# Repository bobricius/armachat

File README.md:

# ARMACHAT
# My network = my rules, no borders, no limits, no operators.

Full time step by step - soldering, programming, assembly

Standalone Doomsday LORA QWERTY communicator

How to restore communication after disaster or Armageddon ? 

It is just hi-tech walkie talkie for fun :)

# Hardware features:

- SAMD21G18 for desktop version (pocket version use SAMD21E18, more easy to solder in TQFP32)
- QWERTY keyboard
 40 keys (4x10) desktop version
 30 keys (5x6) pocket version
- 18650 li-on battery
- 1.8 TFT LCD display 128x160 ST7735
- RFM95 lora module
- 3 freq. by your country
- IRQ / wake up
- Beeper
- Battery charging
- Software RTC with alarms

I shortly tested this messenger in my village and distance is about 500m without direct sight with spread 9.

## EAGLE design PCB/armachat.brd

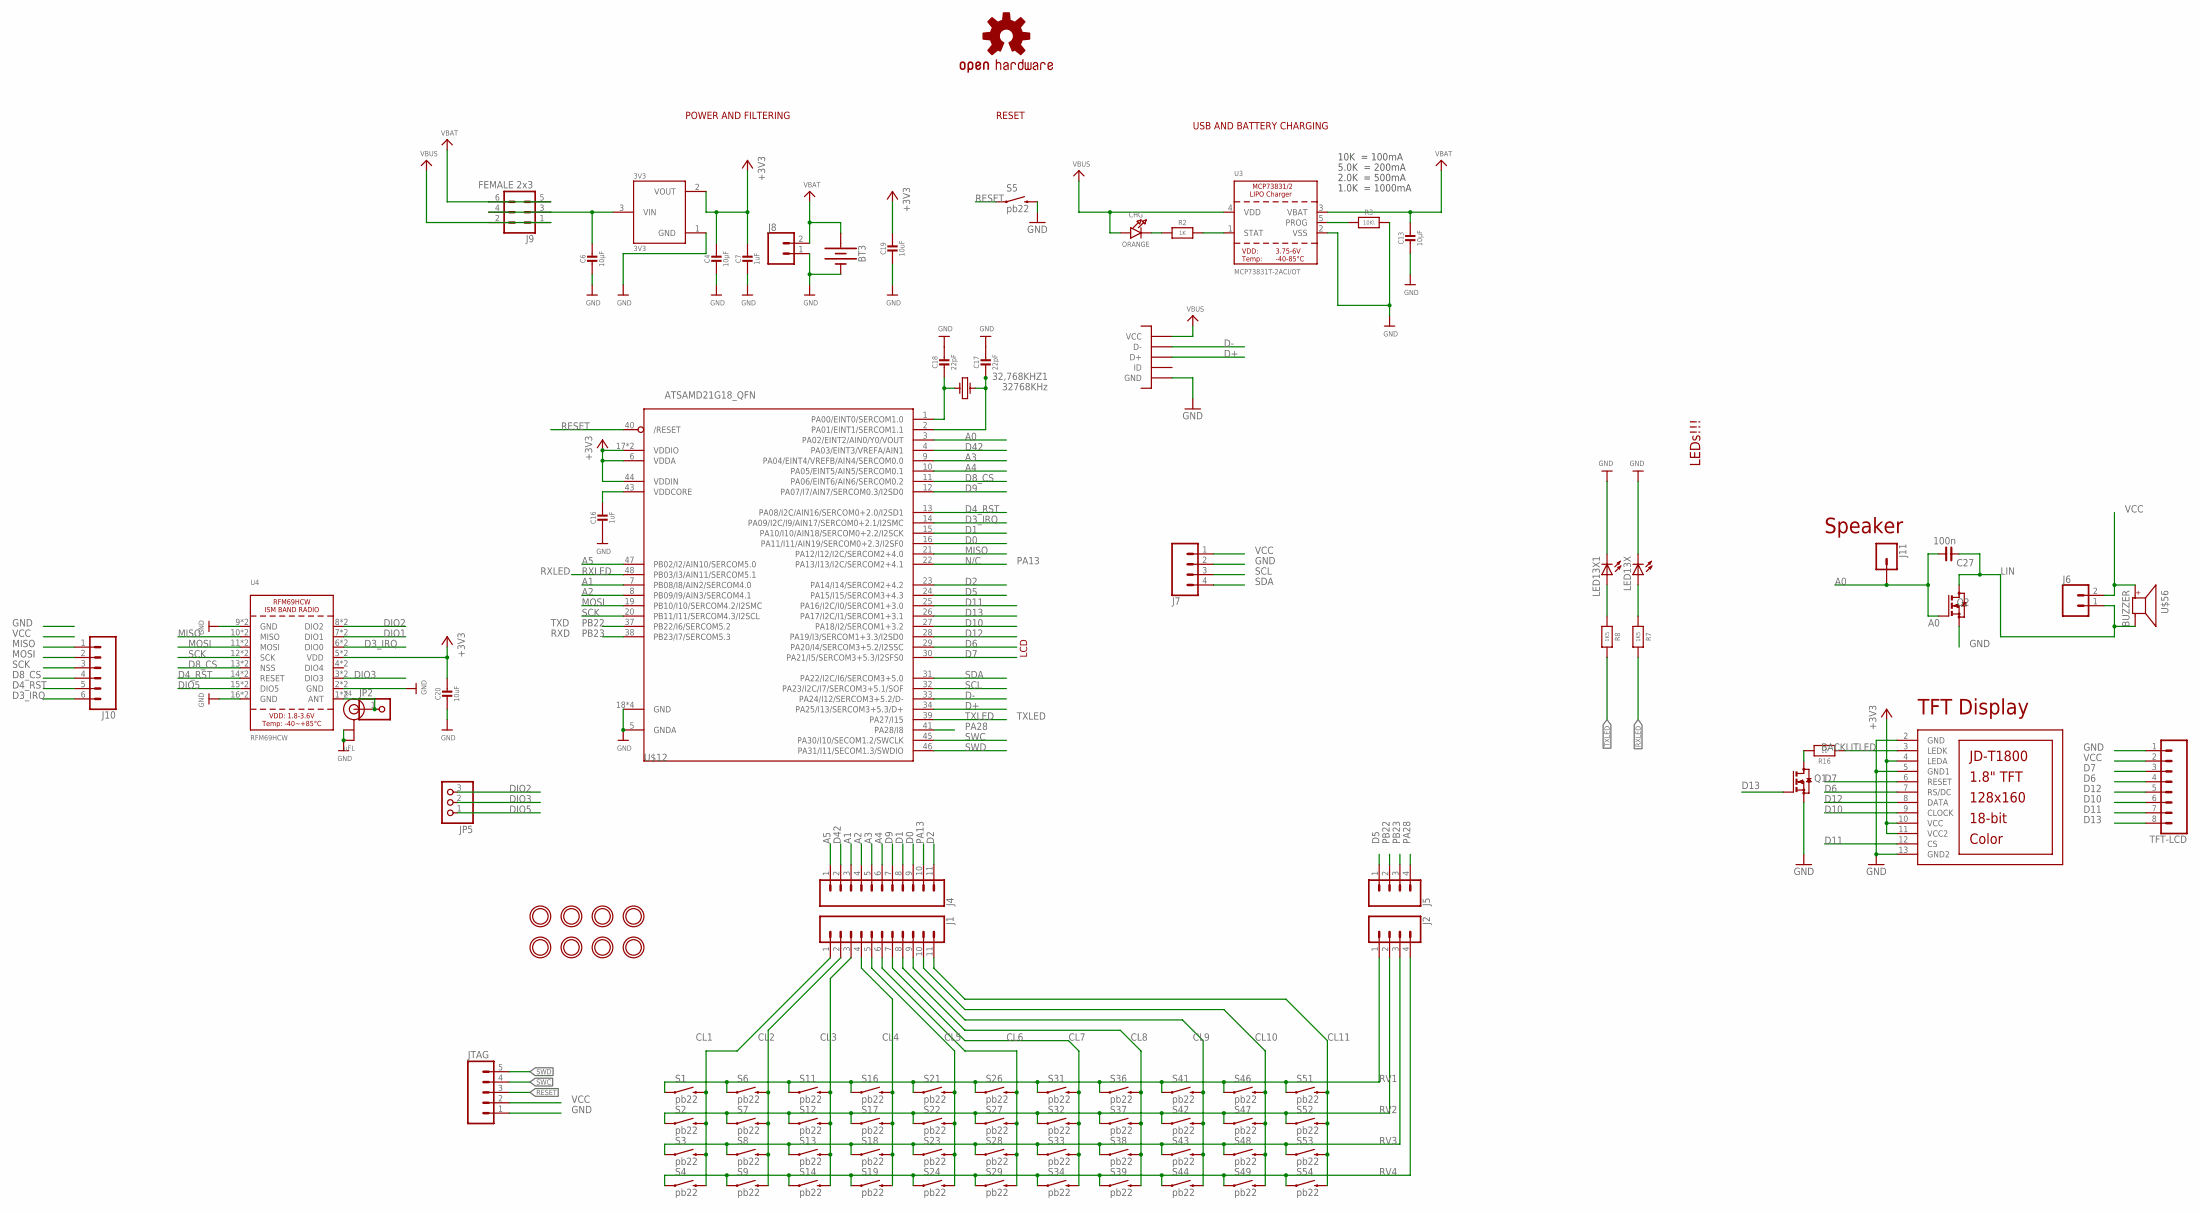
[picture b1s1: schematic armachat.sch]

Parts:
3V3: 3V3; SOT23
32,768KHZ1: 32768KHz; KX-327LT
BT3: BATTERY; 18650_HOLDER_SINGLE_THROUGH-HOLE
C4, C6, C13: 10µF; 0805-NO
C7, C16: 1uF; 0603-NO
C17, C18: 22pF; 0603-NO
C19: 10uF; 0603-NO
C20: 10uF; 0805-NO
C27: 100n; C0603
CHG: ORANGE; CHIPLED_0805_NOOUTLINE
J1, J4: CONN_111X11_NO_SILK; 1X11_NO_SILK
J2, J5, J7: CONN_041X04_NO_SILK; 1X04_NO_SILK
J6, J8: CONN_021X02_NO_SILK; 1X02_NO_SILK
J9: FEMALE 2x3; 2X3
J10: CONN_06NO_SILK_FEMALE_PTH; 1X06_NO_SILK
J11: CONN_01; 1X01
JP2: HEADER-1X1ROUND; 1X01_ROUND
JP5: HEADER-1X3ROUND; 1X03_ROUND
JTAG: M051.27MM; 1X05-1.27MM
LCD1: DISP_LCD_JDT1800; JD-T1800
LED13X, LED13X1: LED3MM
LOGO3: OSHW-LOGOS; OSHW-LOGO-S
Q1, Q2: BSS123; SOT23
R2: 1K; 0603-NO
R3: 10K\; 0603-NO
R7, R8: 1K5; _0603MP
R16: 10; 0603-NO
S1, S2, S3, S4, S6, S7, S8, S9, S11, S12, S13, S14, S16, S17, S18, S19, S21, S22, S23, S24, S26, S27, S28, S29, S31, S32, S33, S34, S36, S37, S38, S39, S41, S42, S43, S44, S46, S47, S48, S49, S51, S52, S53, S54: pb22; TACTILE-PTH
S5: pb22; TACTILE-SWITCH-1101NE
TFT-LCD: CONN_08"; 1X08
U3: MCP73831T-2ACI/OT; SOT23-5
U4: RFM69HCW
U$2, U$3, U$4, U$10, U$11, U$19, U$20, U$42: MOUNTINGHOLE2.0; MOUNTINGHOLE_2.0_PLATED
U$5: MICROUSB; MICRO_B
U$12: ATSAMD21G18_QFN; TQFN48_7MM
U$56: BUZZER; SMT-8585-BUZZER
X4: uFL; U.FL

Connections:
A0: C27.1, J11.1, Q2.1 (G), U$12.3 (PA02/EINT2/AIN0/Y0/VOUT)
A1: J4.3, U$12.7 (PB08/I8/AIN2/SERCOM4.0)
A2: J4.4, U$12.8 (PB09/I9/AIN3/SERCOM4.1)
A3: J4.5, U$12.9 (PA04/EINT4/VREFB/AIN4/SERCOM0.0)
A4: J4.6, U$12.10 (PA05/EINT5/AIN5/SERCOM0.1)
A5: J4.1, U$12.47 (PB02/I2/AIN10/SERCOM5.0)
ANT: JP2.1, U4.1 (ANT), U4.1P (ANT), X4.3 (SIGNAL)
BACKLITLED: LCD1.3 (LEDK), R16.1
CL1: J1.1, S1.3 (2), S2.3 (2), S3.3 (2), S4.3 (2)
CL2: J1.2, S6.3 (2), S7.3 (2), S8.3 (2), S9.3 (2)
CL3: J1.3, S11.3 (2), S12.3 (2), S13.3 (2), S14.3 (2)
CL4: J1.4, S16.3 (2), S17.3 (2), S18.3 (2), S19.3 (2)
CL5: J1.5, S21.3 (2), S22.3 (2), S23.3 (2), S24.3 (2)
CL6: J1.6, S26.3 (2), S27.3 (2), S28.3 (2), S29.3 (2)
CL7: J1.7, S31.3 (2), S32.3 (2), S33.3 (2), S34.3 (2)
CL8: J1.8, S36.3 (2), S37.3 (2), S38.3 (2), S39.3 (2)
CL9: J1.9, S41.3 (2), S42.3 (2), S43.3 (2), S44.3 (2)
CL10: J1.10, S46.3 (2), S47.3 (2), S48.3 (2), S49.3 (2)
CL11: J1.11, S51.3 (2), S52.3 (2), S53.3 (2), S54.3 (2)
D0: J4.9, U$12.16 (PA11/I11/AIN19/SERCOM0+2.3/I2SF0)
D1: J4.8, U$12.15 (PA10/I10/AIN18/SERCOM0+2.2/I2SCK)
D2: J4.11, U$12.23 (PA14/I14/SERCOM2+4.2)
D3_IRQ: J10.6, U4.6 (DIO0), U4.6P (DIO0), U$12.14 (PA09/I2C/I9/AIN17/SERCOM0+2.1/I2SMC)
D4_RST: J10.5, U4.14 (RESET), U4.14P (RESET), U$12.13 (PA08/I2C/AIN16/SERCOM0+2.0/I2SD1)
D5: J5.1, U$12.24 (PA15/I15/SERCOM3+4.3)
D6: LCD1.7 (RS/DC), TFT-LCD.4, U$12.29 (PA20/I4/SERCOM3+5.2/I2SSC)
D7: LCD1.6 (RESET), TFT-LCD.3, U$12.30 (PA21/I5/SERCOM3+5.3/I2SFS0)
D8_CS: J10.4, U4.13 (NSS), U4.13P (NSS), U$12.11 (PA06/EINT6/AIN6/SERCOM0.2)
D9: J4.7, U$12.12 (PA07/I7/AIN7/SERCOM0.3/I2SD0)
D10: LCD1.9 (CLOCK), TFT-LCD.6, U$12.27 (PA18/I2/SERCOM1+3.2)
D11: LCD1.12 (CS), TFT-LCD.7, U$12.25 (PA16/I2C/I0/SERCOM1+3.0)
D12: LCD1.8 (DATA), TFT-LCD.5, U$12.28 (PA19/I3/SERCOM1+3.3/I2SD0)
D13: Q1.1 (G), TFT-LCD.8, U$12.26 (PA17/I2C/I1/SERCOM1+3.1)
D42: J4.2, U$12.4 (PA03/EINT3/VREFA/AIN1)
D+: U$5.P3 (D+), U$12.34 (PA25/I13/SERCOM3+5.3/D+)
D-: U$5.P2 (D-), U$12.33 (PA24/I12/SERCOM3+5.2/D-)
DIO1: U4.7 (DIO1), U4.7P (DIO1)
DIO2: JP5.3, U4.8 (DIO2), U4.8P (DIO2)
DIO3: JP5.2, U4.3 (DIO3), U4.3P (DIO3)
DIO5: JP5.1, U4.15 (DIO5), U4.15P (DIO5)
GND: 3V3.1 (GND), BT3.CON(-) (-), C4.2, C6.2, C7.2, C13.2, C16.2, C17.2, C18.2, C19.2, C20.2, J7.2, J8.1, JTAG.1, LCD1.2 (GND), LCD1.5 (GND1), LCD1.13 (GND2), LED13X.K (C), LED13X1.K (C), Q1.2 (S), Q2.2 (S), R3.2, S5.2, TFT-LCD.1, U3.2 (VSS), U4.2 (GND), U4.2P (GND), U4.9 (GND), U4.9P (GND), U4.16 (GND), U4.16P (GND), U$5.GND1 (GND), U$5.GND2 (GND), U$5.GND3 (GND), U$5.GND4 (GND), U$5.GND7 (GND), U$5.GND8 (GND), U$5.P5 (GND), U$12.5 (GNDA), U$12.18 (GND), U$12.35 (GND), U$12.42 (GND), U$12.THERMAL (GND), X4.1 (GND), X4.2 (GND)
LIN: C27.2, J6.1, Q2.3 (D), U$56.-
MISO: J10.1, U4.10 (MISO), U4.10P (MISO), U$12.21 (PA12/I12/I2C/SERCOM2+4.0)
MOSI: J10.2, U4.11 (MOSI), U4.11P (MOSI), U$12.19 (PB10/I10/SERCOM4.2/I2SMC)
unnamed: 3V3.3 (VIN), C6.1, J9.3, J9.4
unnamed: CHG.C, R2.1
unnamed: R2.2, U3.1 (STAT)
unnamed: R3.1, U3.5 (PROG)
unnamed: LED13X1.A, R8.2
unnamed: 32,768KHZ1.4, C17.1, U$12.2 (PA01/EINT1/SERCOM1.1)
unnamed: 32,768KHZ1.1, C18.1, U$12.1 (PA00/EINT0/SERCOM1.0)
unnamed: Q1.3 (D), R16.2
unnamed: LED13X.A, R7.2
PA13: J4.10, U$12.22 (PA13/I13/I2C/SERCOM2+4.1)
PA28: J5.4, U$12.41 (PA28/I8)
PB22: J5.2, U$12.37 (PB22/I6/SERCOM5.2)
PB23: J5.3, U$12.38 (PB23/I7/SERCOM5.3)
RESET: JTAG.3, S5.1, U$12.40 (/RESET)
RV1: J2.1, S1.1, S6.1, S11.1, S16.1, S21.1, S26.1, S31.1, S36.1, S41.1, S46.1, S51.1
RV2: J2.2, S2.1, S7.1, S12.1, S17.1, S22.1, S27.1, S32.1, S37.1, S42.1, S47.1, S52.1
RV3: J2.3, S3.1, S8.1, S13.1, S18.1, S23.1, S28.1, S33.1, S38.1, S43.1, S48.1, S53.1
RV4: J2.4, S4.1, S9.1, S14.1, S19.1, S24.1, S29.1, S34.1, S39.1, S44.1, S49.1, S54.1
RXLED: R7.1, U$12.48 (PB03/I3/AIN11/SERCOM5.1)
SCK: J10.3, U4.12 (SCK), U4.12P (SCK), U$12.20 (PB11/I11/SERCOM4.3/I2SCL)
SCL: J7.3, U$12.32 (PA23/I2C/I7/SERCOM3+5.1/SOF)
SDA: J7.4, U$12.31 (PA22/I2C/I6/SERCOM3+5.0)
SWC: JTAG.4, U$12.45 (PA30/I10/SECOM1.2/SWCLK)
SWD: JTAG.5, U$12.46 (PA31/I11/SECOM1.3/SWDIO)
TXLED: R8.1, U$12.39 (PA27/I15)
VBAT: BT3.CON(+) (+), C13.1, J8.2, J9.5, J9.6, U3.3 (VBAT)
VBUS: CHG.A, J9.1, J9.2, U3.4 (VDD), U$5.P1 (VCC)
VCC: 3V3.2 (VOUT), C4.1, C7.1, C19.1, C20.1, J6.2, J7.1, JTAG.2, LCD1.4 (LEDA), LCD1.10 (VCC), LCD1.11 (VCC2), TFT-LCD.2, U4.5 (VDD), U4.5P (VDD), U$12.6 (VDDA), U$12.17 (VDDIO), U$12.36 (VDDIO), U$12.44 (VDDIN), U$56.+
VDDCORE1: C16.1, U$12.43 (VDDCORE)

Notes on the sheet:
LEDs!!!
POWER AND FILTERING
RESET
10K = 100mA
5.0K = 200mA
2.0K = 500mA
1.0K = 1000mA
N/C
TXLED
RXLED
TXD
RXD
USB AND BATTERY CHARGING
TFT Display
Speaker
LCD

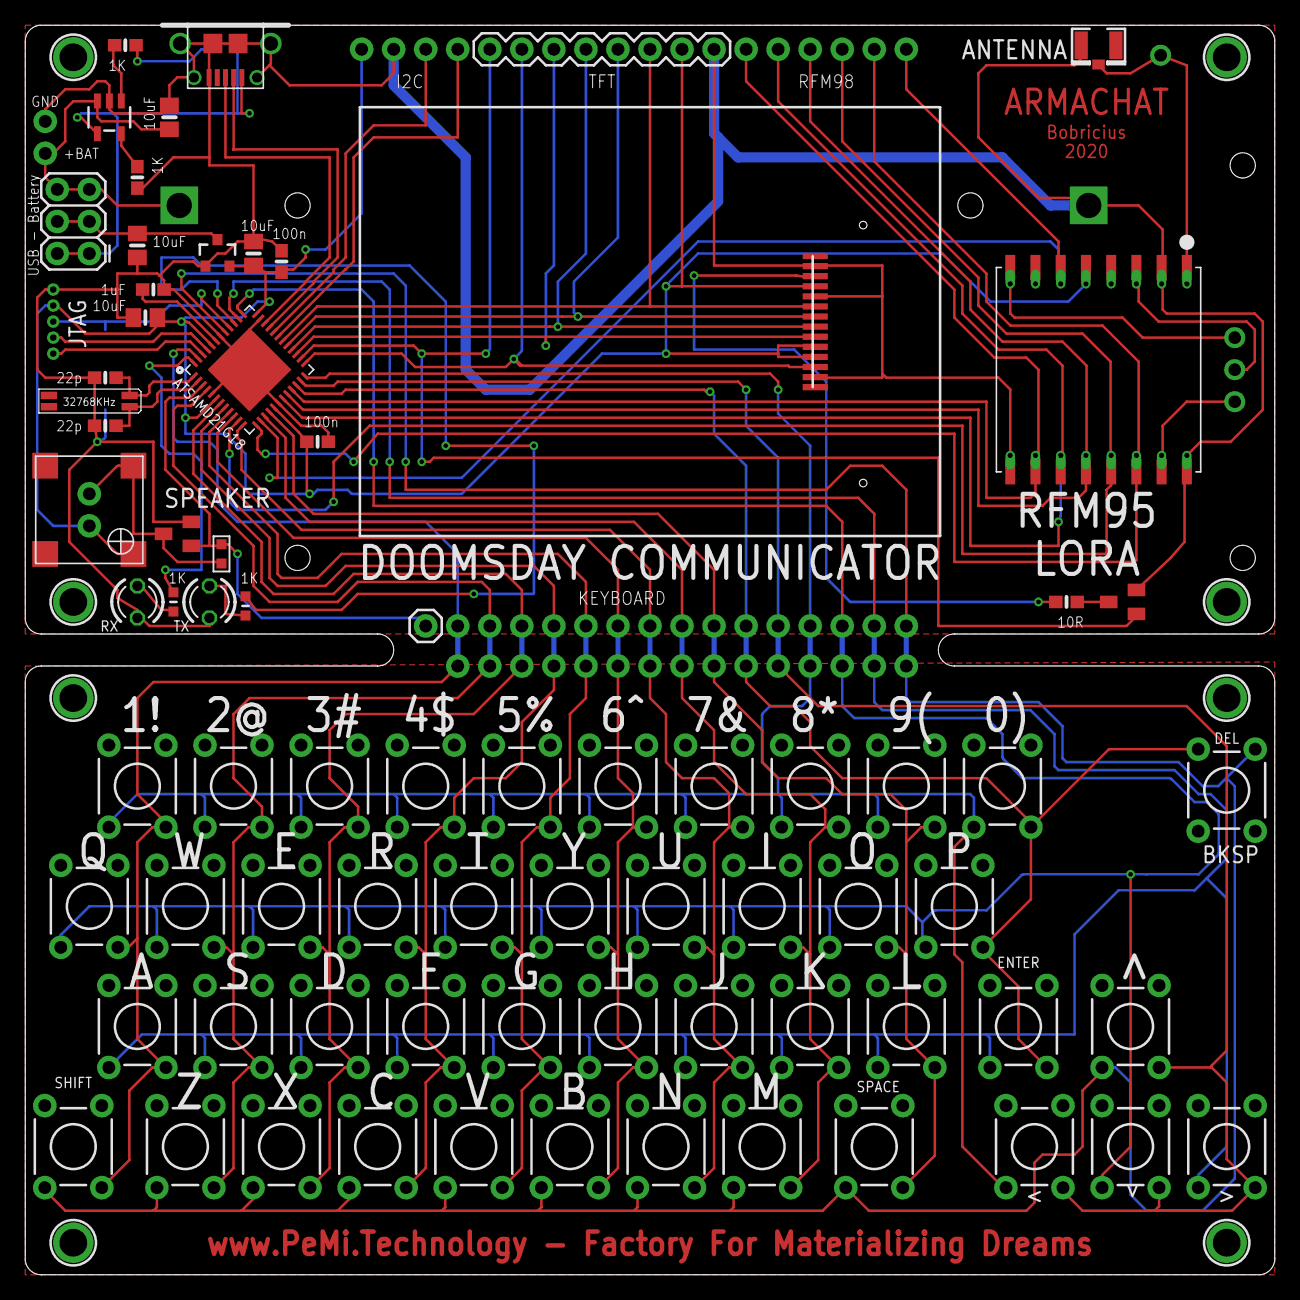
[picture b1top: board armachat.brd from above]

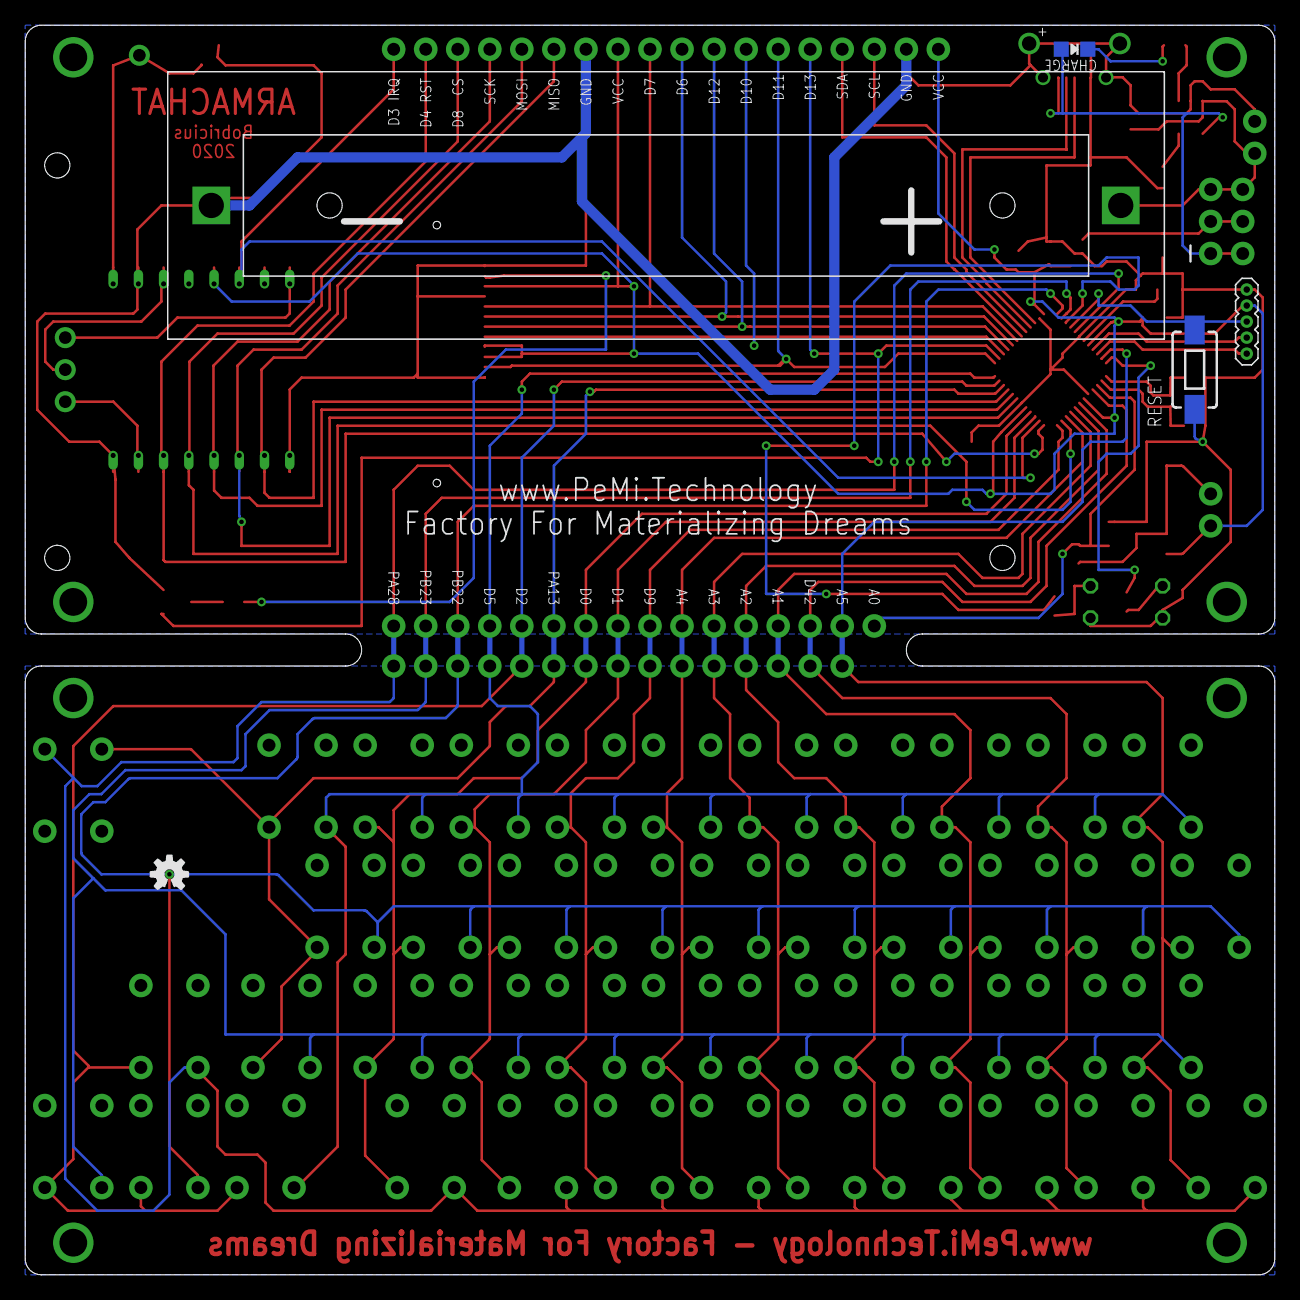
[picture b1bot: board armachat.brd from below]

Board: 2 copper layers, 99.1 x 99.1 mm, 98 parts (5 on the bottom side), 73 nets.

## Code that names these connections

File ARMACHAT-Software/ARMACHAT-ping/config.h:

#define KEY_SHIFT 2
#define KEY_UP 3
#define KEY_LEFT 4
#define KEY_DOWN 5
#define KEY_RIGHT 6
#define KEY_RETURN 10
#define KEY_DELETE 8

#define PORT_IOBUS

#define white ST77XX_WHITE
#define black ST77XX_BLACK
#define red ST77XX_RED
#define blue ST77XX_BLUE
#define green ST77XX_GREEN
#define yellow ST77XX_YELLOW
#define magenta ST77XX_MAGENTA
#define cyan ST77XX_CYAN

#ifdef FUSION
// FUSION communicator version with SAMD21E18
// require samd core from https://github.com/mattairtech/ArduinoCore-samd/tree/master/variants/MT_D21E_revB
const int csPin = 23;         // LoRa radio chip select signal
const int resetPin = -1;       // LoRa radio reset
const int irqPin = 9;         // change for your board; must be a hardware interrupt pin
//******************** display
#define TFT_CS        -1 //11 // PyBadge/PyGamer display control pins: chip select
#define TFT_RST       -1 // Display reset
#define TFT_DC        27 // Display data/command select
#define TFT_BACKLIGHT 10 // Display backlight pin
#define TFT_MOSI 14  // Data out
#define TFT_SCLK 15  // Clock out

#define speaker       2 // Speaker
const byte ROWS = 6; // rows
const byte COLS = 5; // columns
byte colPins[COLS] = {30, 31, 28, 0, 1}; //pa13-d38,connect to the row pinouts of the keypad
byte rowPins[ROWS] = {3, 4, 5, 6, 7, 8}; //pb22-d30,pb23-d31,pa28-d27 connect to the column pinouts of the keypad
//define the symbols on the buttons of the keypads
char directKeys[ROWS][COLS] = {
  {KEY_RETURN, ' ', 'm', 'n', 'b',},
  {KEY_DELETE, 'l', 'k', 'j', 'h',},
  {'p', 'o', 'i', 'u', 'y',},
  {KEY_SHIFT, 'z', 'x', 'c', 'v',},
  {'a', 's', 'd', 'f', 'g',},
  {'q', 'w', 'e', 'r', 't',}  
};
char shiftKeys[ROWS][COLS] = {
  {KEY_RIGHT, ',', 'M', 'N', 'B',},
  {KEY_LEFT, 'L', 'K', 'J', 'H',},
  {'P', 'O', 'I', 'U', 'Y',},
  {KEY_SHIFT, 'Z', 'X', 'C', 'V',},
  {'A', 'S', 'D', 'F', 'G',},
  {'Q', 'W', 'E', 'R', 'T',}  
};

char symbolKeys[ROWS][COLS] = {
  {KEY_RIGHT, '.', ':', ';', '""',},
  {KEY_LEFT, ':', '*', '&', '^',},
  {'0', '9', '8', '7', '6',},
  {KEY_SHIFT, '(', ')', '?', '/',},
  {'!', '@', '#', '$', '%',},
  {'1', '2', '3', '4', '5',}  
};
#endif
//----------------------------------------------------------------------------------------------------------------------

//******************** display
#ifdef LCDTFT
Adafruit_ST7735 tft = Adafruit_ST7735(&SPI1, TFT_CS, TFT_DC, TFT_RST);
#endif

#ifdef LCDIPS
Adafruit_ST7789 tft = Adafruit_ST7789(&SPI1, TFT_CS, TFT_DC, TFT_RST);
#endif

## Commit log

2020-04-12 PCB design files
2020-04-12 Front Panel
2020-04-21 Add files via upload
    First usable working version
2020-08-11 Add files via upload
    Latest version
2020-08-12 Case STL and blend files plus photos
2020-08-15 Bootloader and Firmware
2020-08-18 Added support to mute sound
2020-08-19 use menuUp to set sound settings
2020-08-19 Fix send message confirmation dialog.
    tidy up code
2021-01-15 Add files via upload
    Updating libraries, and precompiled ready to use firmware. And my "DIY" alternative to ATMEL-ICE
2024-05-10 Update config.h
    commit test

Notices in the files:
parts and their libraries:
SparkFun-Aesthetics: Licensing: Creative Commons ShareAlike 4.0 International - https://creativecommons.org/licenses/by-sa/4.0
